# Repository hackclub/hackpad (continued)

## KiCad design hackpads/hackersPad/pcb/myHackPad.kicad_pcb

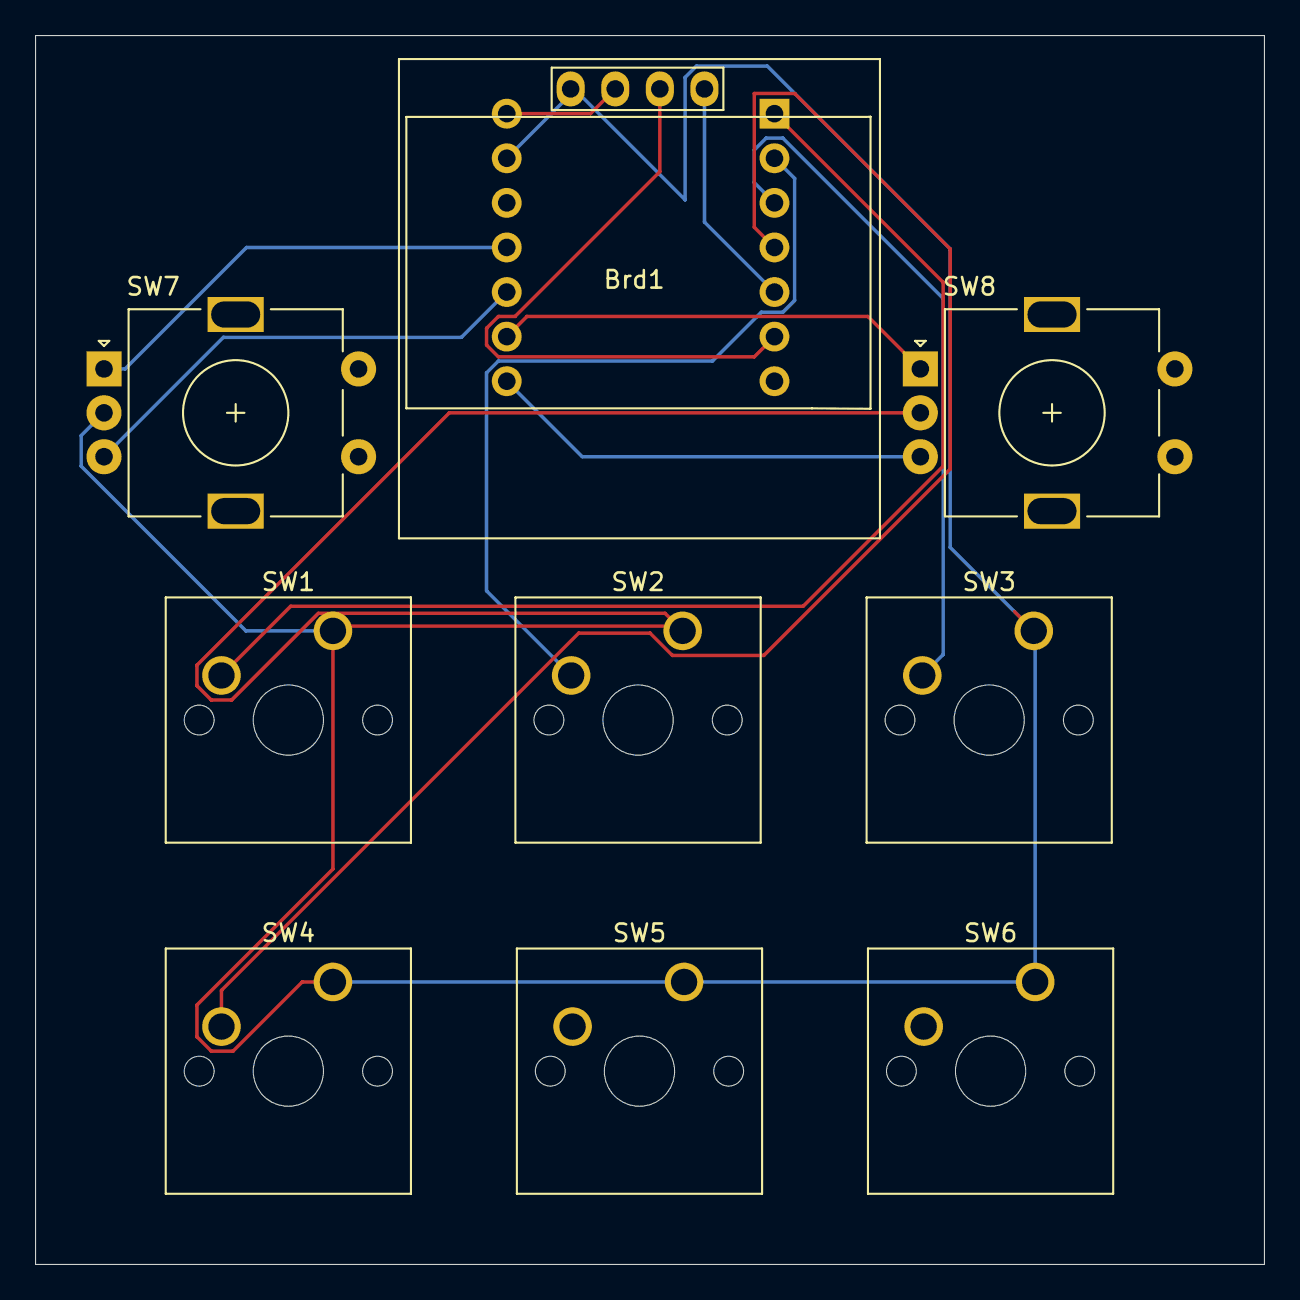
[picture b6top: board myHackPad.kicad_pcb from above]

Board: 2 copper layers, 70.0 x 70.0 mm, 10 parts (1 on the bottom side), 12 nets.

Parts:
Brd1: SSD1306; 128x64OLED
SW1, SW2, SW3, SW4, SW5, SW6: SW_Push; SW_Cherry_MX_1.00u_PCB
SW7, SW8: RotaryEncoder; RotaryEncoder_Alps_EC11E-Switch_Vertical_H20mm
U1: Seeed Studio XIAO SAMD21; XIAO-Generic-Thruhole-14P-2.54-21X17.8MM

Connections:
GND: Brd1.1 (GND), SW1.1, SW2.1, SW3.1, SW4.1, SW5.1, SW6.1, SW7.C, SW8.C, U1.13 (GND)
S1: SW1.2, U1.1 (PA02_A0_D0)
S2: SW2.2, U1.2 (PA4_A1_D1)
S3: SW3.2, U1.3 (PA10_A2_D2)
S4: SW4.2, U1.4 (PA11_A3_D3)
S7A: SW7.A, U1.11 (PA6_A10_D10_MOSI)
S7B: SW7.B, U1.10 (PA5_A9_D9_MISO)
S8A: SW8.A, U1.9 (PA7_A8_D8_SCK)
S8B: SW8.B, U1.8 (PB09_A7_D7_RX)
SCL: Brd1.3 (SCL), U1.6 (PA9_A5_D5_SCL)
SDA: Brd1.4 (SDA), U1.5 (PA8_A4_D4_SDA)
VCC: Brd1.2 (VCC), U1.14 (5V)

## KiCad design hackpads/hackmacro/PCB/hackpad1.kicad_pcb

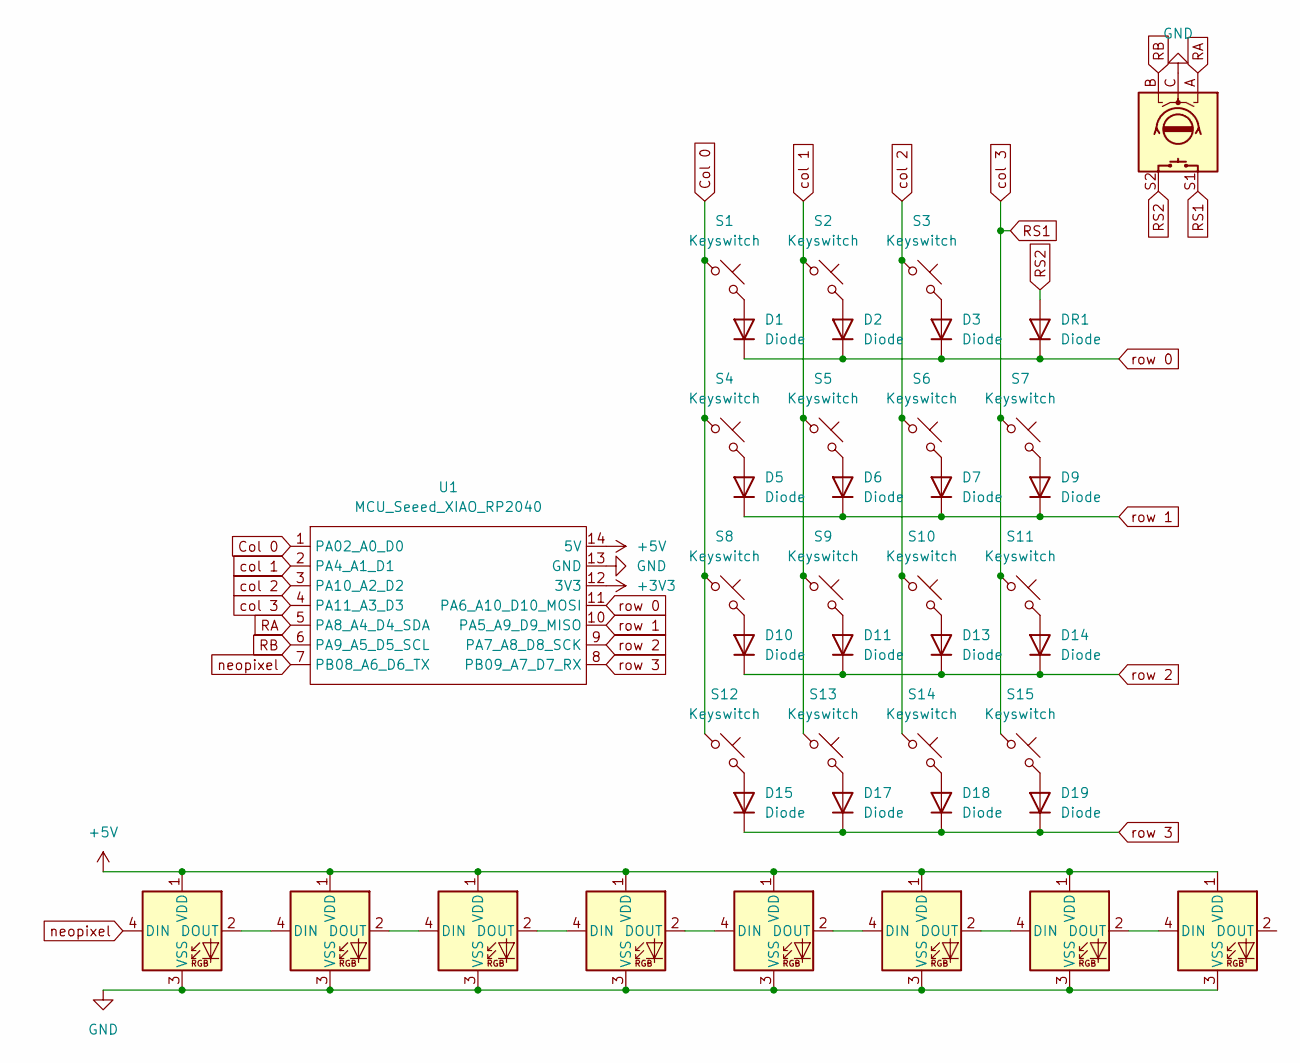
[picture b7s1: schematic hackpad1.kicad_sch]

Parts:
D1, D2, D3, D5, D6, D7, D9, D10, D11, D13, D14, D15, D17, D18, D19: Diode; Diode_DO-35
D4, D8, D12, D16, D20, D21, D22, D23: LED_WS2812B
DR1: Diode; Diode_DO-35
S1, S2, S3, S4, S5, S6, S7, S8, S9, S10, S11, S12, S13, S14, S15: Keyswitch; Choc_V1V2_1.00u
SW1: RotaryEncoder_Switch; Encoder_EC11_MX
U1: MCU_Seeed_XIAO_RP2040; Seeed_XIAO_RP2040

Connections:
+3V3: U1.12 (3V3)
+5V: D4.1 (VDD), D8.1 (VDD), D12.1 (VDD), D16.1 (VDD), D20.1 (VDD), D21.1 (VDD), D22.1 (VDD), D23.1 (VDD), U1.14 (5V); also elsewhere on the board
Col 0: S1.1, S4.1, S8.1, S12.1, U1.1 (PA02_A0_D0)
GND: D4.3 (VSS), D8.3 (VSS), D12.3 (VSS), D16.3 (VSS), D20.3 (VSS), D21.3 (VSS), D22.3 (VSS), D23.3 (VSS), SW1.C, U1.13 (GND); also elsewhere on the board
unnamed: D1.2 (A), S1.2
unnamed: D2.2 (A), S2.2
unnamed: D3.2 (A), S3.2
unnamed: D4.2 (DOUT), D8.4 (DIN)
unnamed: D5.2 (A), S4.2
unnamed: D6.2 (A), S5.2
unnamed: D7.2 (A), S6.2
unnamed: D9.2 (A), S7.2
unnamed: D10.2 (A), S8.2
unnamed: D11.2 (A), S9.2
unnamed: D8.2 (DOUT), D12.4 (DIN)
unnamed: D12.2 (DOUT), D16.4 (DIN)
unnamed: D13.2 (A), S10.2
unnamed: D14.2 (A), S11.2
unnamed: D15.2 (A), S12.2
unnamed: D16.2 (DOUT), D20.4 (DIN)
unnamed: D17.2 (A), S13.2
unnamed: D18.2 (A), S14.2
unnamed: D19.2 (A), S15.2
unnamed: D20.2 (DOUT), D21.4 (DIN)
unnamed: D21.2 (DOUT), D22.4 (DIN)
unnamed: D22.2 (DOUT), D23.4 (DIN)
unnamed 26: D23.2 (DOUT); also elsewhere on the board
RA: SW1.A, U1.5 (PA8_A4_D4_SDA)
RB: SW1.B, U1.6 (PA9_A5_D5_SCL)
RS1: S7.1, S11.1, S15.1, SW1.S1, U1.4 (PA11_A3_D3)
RS2: DR1.2 (A), SW1.S2
col 1: S2.1, S5.1, S9.1, S13.1, U1.2 (PA4_A1_D1)
col 2: S3.1, S6.1, S10.1, S14.1, U1.3 (PA10_A2_D2)
neopixel: D4.4 (DIN), U1.7 (PB08_A6_D6_TX)
row 0: D1.1 (K), D2.1 (K), D3.1 (K), DR1.1 (K), U1.11 (PA6_A10_D10_MOSI)
row 1: D5.1 (K), D6.1 (K), D7.1 (K), D9.1 (K), U1.10 (PA5_A9_D9_MISO)
row 2: D10.1 (K), D11.1 (K), D13.1 (K), D14.1 (K), U1.9 (PA7_A8_D8_SCK)
row 3: D15.1 (K), D17.1 (K), D18.1 (K), D19.1 (K), U1.8 (PB09_A7_D7_RX)

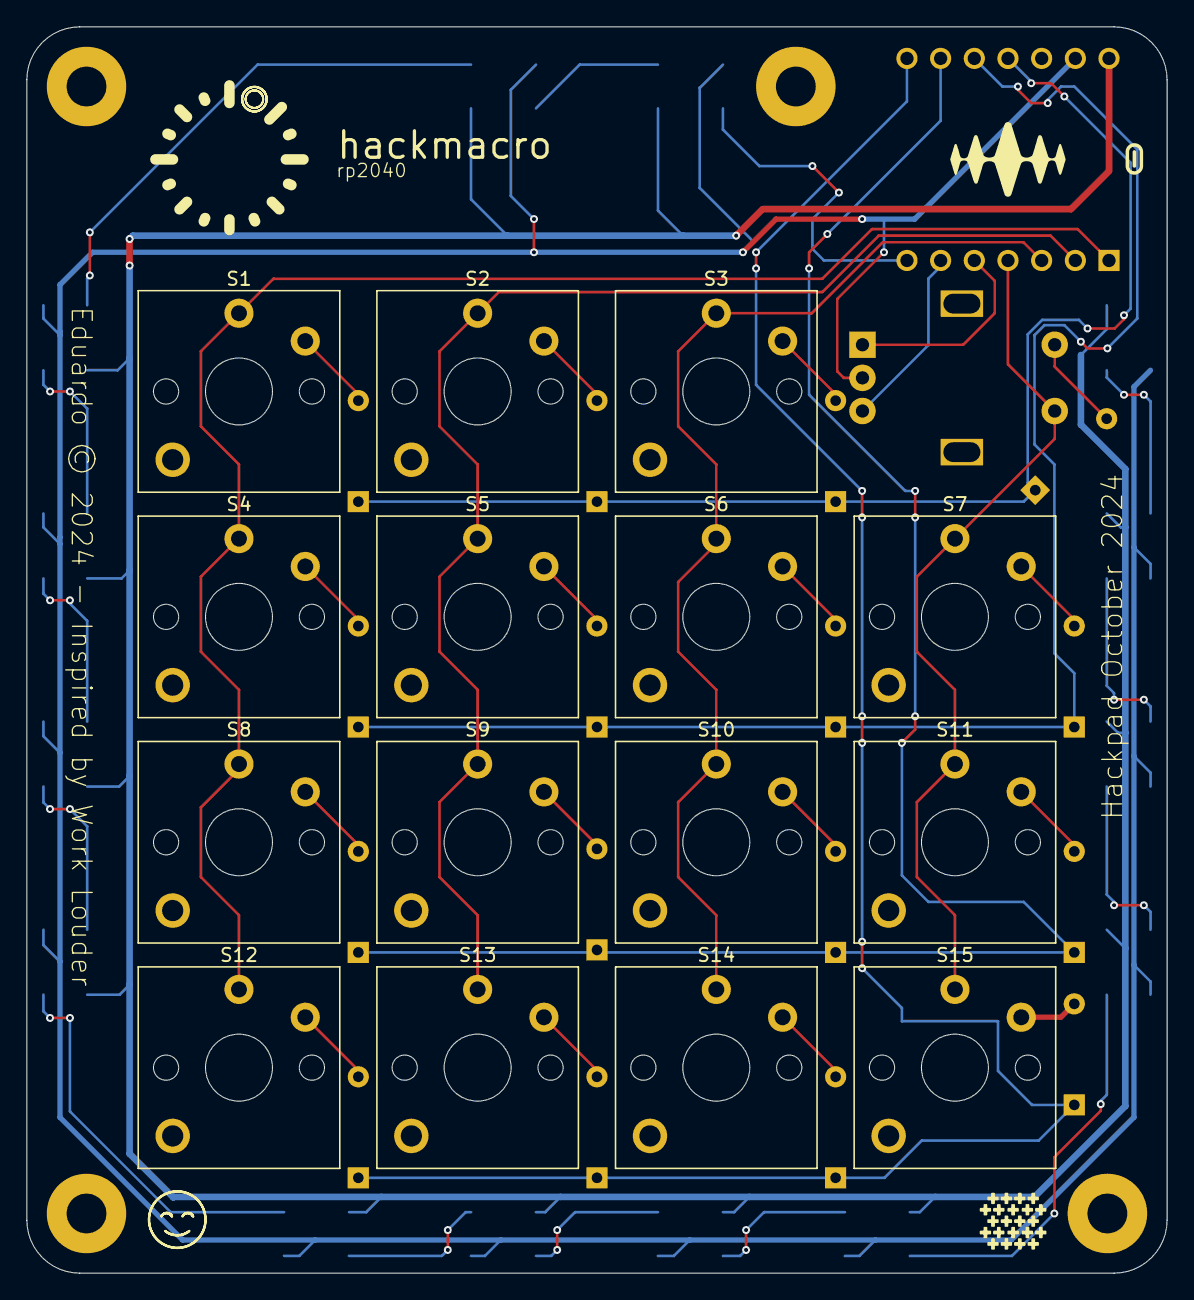
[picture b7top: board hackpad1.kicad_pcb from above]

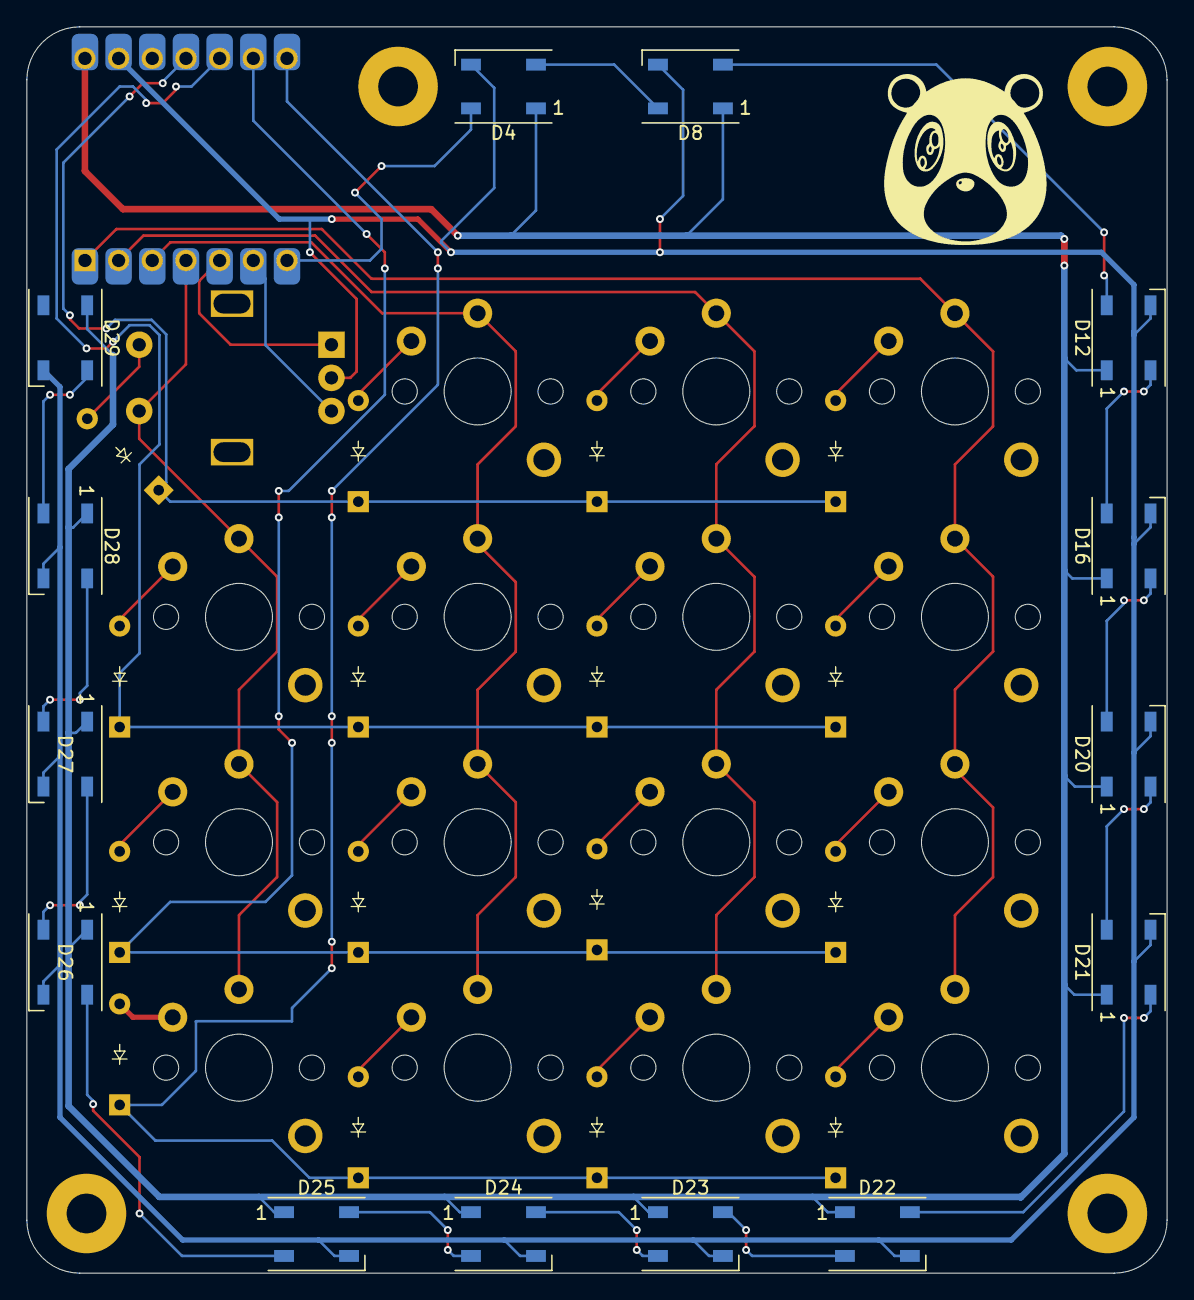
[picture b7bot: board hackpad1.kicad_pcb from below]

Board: 2 copper layers, 86.0 x 94.0 mm, 47 parts (31 on the bottom side), 42 nets.

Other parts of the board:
D24, D25, D26, D27, D28, D29: LED_WS2812B

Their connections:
+5V: D24.1 (VDD), D25.1 (VDD), D26.1 (VDD), D27.1 (VDD), D28.1 (VDD), D29.1 (VDD); also elsewhere on the board
GND: D24.3 (VSS), D25.3 (VSS), D26.3 (VSS), D27.3 (VSS), D28.3 (VSS), D29.3 (VSS); also elsewhere on the board
unnamed 26: D24.4 (DIN); also elsewhere on the board
unnamed: D24.2 (DOUT), D25.4 (DIN)
unnamed: D25.2 (DOUT), D26.4 (DIN)
unnamed: D26.2 (DOUT), D27.4 (DIN)
unnamed: D27.2 (DOUT), D28.4 (DIN)
unnamed: D28.2 (DOUT), D29.4 (DIN)
